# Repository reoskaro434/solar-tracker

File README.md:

# solar-tracker

You can check presentation of the device by clicking the link below:

https://youtu.be/ewcDlxyHeMo

Topic:

Solar Tracker Moving the Panel Towards Light.

Description:

The device rotates the solar panel towards the most intense light source.
The solar panel charges a battery, which can be used to charge other devices.
The display shows the current battery charge level and the current voltage generated by the solar panel.

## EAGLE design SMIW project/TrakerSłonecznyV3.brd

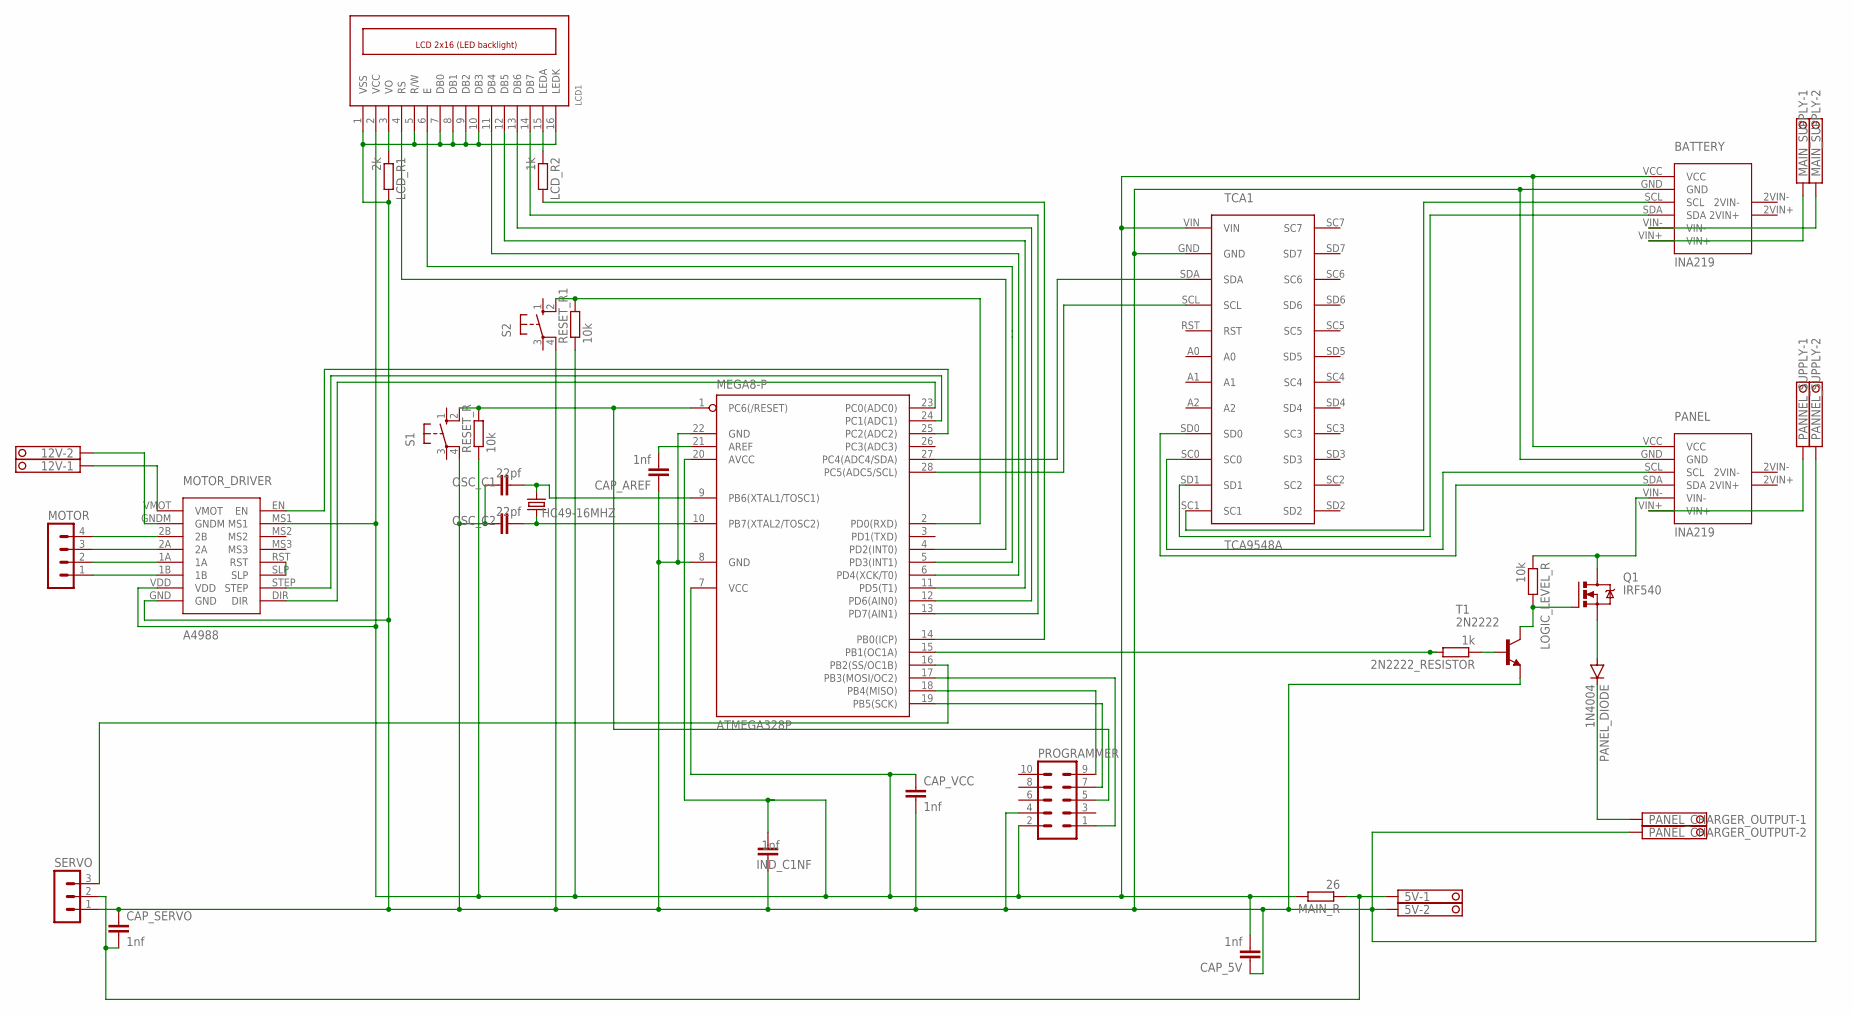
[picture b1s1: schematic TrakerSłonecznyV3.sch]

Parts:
2N2222_RESISTOR: 1k; 0207/2V
5V, 12V: TERMINAL-BLOCK-3.5MM-2-PIN-ROUND-PAD; TERMINAL-BLOCK-2-PIN-3.5MM-ROUND-PAD
ATMEGA328P: MEGA8-P; DIL28-3
BATTERY: INA219
CAP_5V: 1nf; C025-024X044
CAP_AREF: 1nf; C025-024X044
CAP_SERVO: 1nf; C025-024X044
CAP_VCC: 1nf; C025-024X044
HC49-16MHZ: CRYTALHC49S; HC49/S
IND_C1NF: 1nf; C025-024X044
LCD1: LCD_2X16_SIL; HY-1602F
LCD_R1: 2k; 0207/2V
LCD_R2: 1k; 0207/2V
LOGIC_LEVEL_R: 10k; 0207/2V
MAIN_R: 26; 0207/2V
MAIN_SUPPLY: TERMINAL-BLOCK-3.5MM-2-PIN-ROUND-PAD; TERMINAL-BLOCK-2-PIN-3.5MM-ROUND-PAD
MOTOR: MA04-1
MOTOR_DRIVER: A4988
OSC_C1, OSC_C2: 22pf; C025-024X044
PANEL: INA219
PANEL_CHARGER_OUTPUT: TERMINAL-BLOCK-3.5MM-2-PIN-ROUND-PAD; TERMINAL-BLOCK-2-PIN-3.5MM-ROUND-PAD
PANEL_DIODE: 1N4004; DO41-10
PANNEL_SUPPLY: TERMINAL-BLOCK-3.5MM-2-PIN-ROUND-PAD; TERMINAL-BLOCK-2-PIN-3.5MM-ROUND-PAD
PROGRAMMER: MA05-2
Q1: IRF540; TO220BV
RESET_R, RESET_R1: 10k; 0207/2V
S1, S2: 10-XX; B3F-10XX
SERVO: MA03-1
T1: 2N2222; TO92-EBC-OVAL
TCA1: TCA9548A

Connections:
5V: ATMEGA328P.7 (VCC), ATMEGA328P.20 (AVCC), BATTERY.VCC, CAP_5V.2, CAP_VCC.1, IND_C1NF.2, LCD1.2 (VCC), MAIN_R.2, MOTOR_DRIVER.MS1, MOTOR_DRIVER.VDD, PANEL.VCC, PROGRAMMER.2, RESET_R.1, RESET_R1.1, TCA1.VIN
GND: 5V.2, ATMEGA328P.8 (GND), ATMEGA328P.22 (GND), BATTERY.GND, CAP_5V.1, CAP_AREF.1, CAP_SERVO.1, CAP_VCC.2, IND_C1NF.1, LCD1.1 (VSS), LCD1.5 (R/W), LCD1.7 (DB0), LCD1.8 (DB1), LCD1.9 (DB2), LCD1.10 (DB3), LCD1.16 (LEDK), LCD_R1.2, MOTOR_DRIVER.GND, OSC_C1.1, OSC_C2.1, PANEL.GND, PANEL_CHARGER_OUTPUT.2, PANNEL_SUPPLY.2, PROGRAMMER.4, S1.4 (P1), S2.4 (P1), SERVO.1, T1.E, TCA1.GND
unnamed: BATTERY.SCL, TCA1.SC1
unnamed: ATMEGA328P.9 (PB6(XTAL1/TOSC1)), HC49-16MHZ.1, OSC_C1.2
unnamed: ATMEGA328P.10 (PB7(XTAL2/TOSC2)), HC49-16MHZ.2, OSC_C2.2
unnamed: 2N2222_RESISTOR.2, ATMEGA328P.15 (PB1(OC1A))
unnamed: ATMEGA328P.16 (PB2(SS/OC1B)), SERVO.3
unnamed: 5V.1, CAP_SERVO.2, MAIN_R.1, SERVO.2
unnamed: BATTERY.SDA, TCA1.SD1
unnamed: ATMEGA328P.6 (PD4(XCK/T0)), LCD1.11 (DB4)
unnamed: MOTOR.1, MOTOR_DRIVER.1B
unnamed: MOTOR.2, MOTOR_DRIVER.1A
unnamed: ATMEGA328P.11 (PD5(T1)), LCD1.12 (DB5)
unnamed: ATMEGA328P.12 (PD6(AIN0)), LCD1.13 (DB6)
unnamed: ATMEGA328P.13 (PD7(AIN1)), LCD1.14 (DB7)
unnamed: PANEL.SDA, TCA1.SD0
unnamed: PANEL.SCL, TCA1.SC0
unnamed: MOTOR.3, MOTOR_DRIVER.2A
unnamed: PANEL.VIN+, PANNEL_SUPPLY.1
unnamed: ATMEGA328P.4 (PD2(INT0)), LCD1.4 (RS)
unnamed: BATTERY.VIN+, MAIN_SUPPLY.1
unnamed: ATMEGA328P.27 (PC4(ADC4/SDA)), TCA1.SDA
unnamed: ATMEGA328P.28 (PC5(ADC5/SCL)), TCA1.SCL
unnamed: BATTERY.VIN-, MAIN_SUPPLY.2
unnamed: LOGIC_LEVEL_R.1, PANEL.VIN-, Q1.D
unnamed: ATMEGA328P.14 (PB0(ICP)), LCD_R2.2
unnamed: ATMEGA328P.21 (AREF), CAP_AREF.2
unnamed: ATMEGA328P.1 (PC6(/RESET)), PROGRAMMER.5, RESET_R.2, S1.2 (S1)
unnamed: MOTOR.4, MOTOR_DRIVER.2B
unnamed: LOGIC_LEVEL_R.2, Q1.G, T1.C
unnamed: 12V.2, MOTOR_DRIVER.GNDM
unnamed: 12V.1, MOTOR_DRIVER.VMOT
unnamed: MOTOR_DRIVER.RST, MOTOR_DRIVER.SLP
unnamed: ATMEGA328P.23 (PC0(ADC0)), MOTOR_DRIVER.DIR
unnamed: ATMEGA328P.24 (PC1(ADC1)), MOTOR_DRIVER.STEP
unnamed: ATMEGA328P.25 (PC2(ADC2)), MOTOR_DRIVER.EN
unnamed: 2N2222_RESISTOR.1, T1.B
unnamed: ATMEGA328P.2 (PD0(RXD)), RESET_R1.2, S2.2 (S1)
unnamed: PANEL_CHARGER_OUTPUT.1, PANEL_DIODE.C
unnamed: PANEL_DIODE.A, Q1.S
unnamed: LCD1.15 (LEDA), LCD_R2.1
unnamed: ATMEGA328P.17 (PB3(MOSI/OC2)), PROGRAMMER.1
unnamed: ATMEGA328P.19 (PB5(SCK)), PROGRAMMER.7
unnamed: ATMEGA328P.18 (PB4(MISO)), PROGRAMMER.9
unnamed: ATMEGA328P.5 (PD3(INT1)), LCD1.6 (E)
unnamed: LCD1.3 (VO), LCD_R1.1

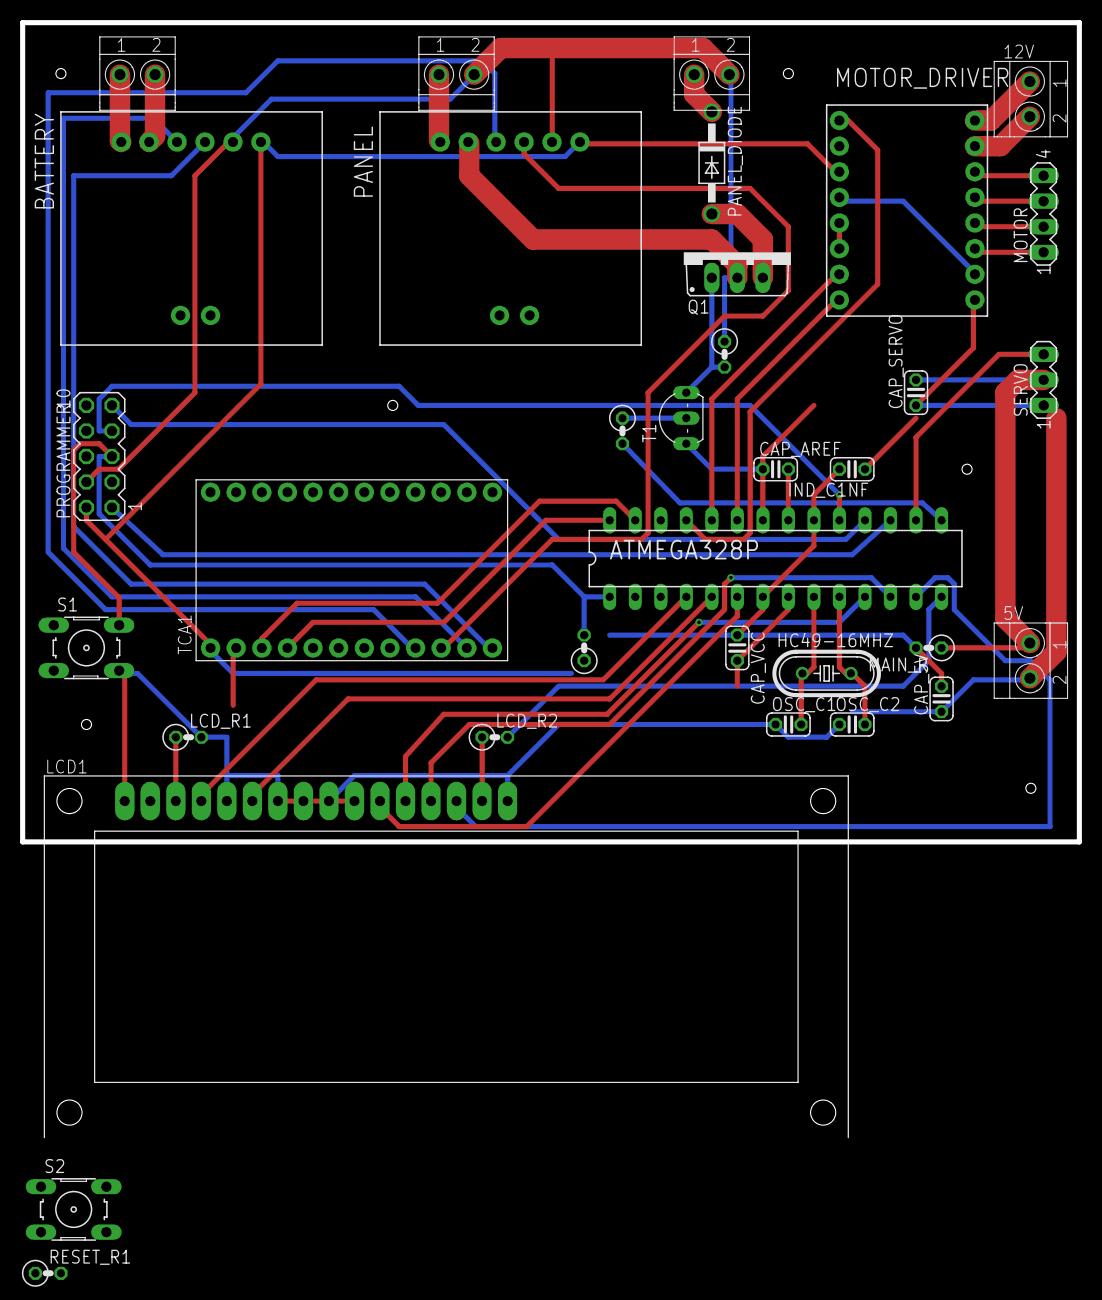
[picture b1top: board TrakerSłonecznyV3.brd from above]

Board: 2 copper layers, 105.2 x 81.5 mm, 34 parts (0 on the bottom side), 46 nets.

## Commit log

2021-01-19 created sun tracking
2021-01-20 fixed charging problem
    Sometimes battery charging was disabling.
2021-01-31 Improved sun tracking
2021-01-31 hotfix
    fixed bad sun tracking, whent the sun was on the right side of panel
2021-02-02 fixed small elements
2021-02-07 commented code
2021-04-02 documentation
2023-10-11 Updated language
